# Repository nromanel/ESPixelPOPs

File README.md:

# ESPixel Pops

This is an attempted re-creation based on the original materials. It is not
the author's released board file.

A one-output Wi-Fi pixel controller for an ESP-01 module. The circuit is the
Ukewarrior ESPixel Pops rev D schematic of 19 July 2017. The board is 1.80 by
1.00 inch, so the 1.00 inch side slides into 1 inch schedule-40 PVC.

Every part on the board is through-hole. Open `ESPixelPOPs.kicad_pcb` in KiCad
8 and run Edit, Fill All Zones before ordering. GND is already traced on the
back; the zone is the pour.

- [ESPixel Pops project](https://zappedmyself.com/projects/espixelpops/) — [@packetbob](https://github.com/packetbob)
- [Original ESPixel](https://github.com/madsci1016/ESPixel) — [@madsci1016](https://github.com/madsci1016)

## How it matches the build guide

J1 is the 5-position 3.81 mm terminal, wire entries facing off the left edge.

| Pin | Silk | Connect |
|---|---|---|
| 1 | VCC | supply positive |
| 2 | GND | supply negative |
| 3 | GND | pixel ground |
| 4 | DATA | pixel data |
| 5 | VCC | pixel positive |

JP1 reads GND, CTS, VCC, RX, TX, DTR from left to right. For programming,
connect adapter ground to GND, adapter TXD to RX, and adapter RXD to TX. Leave
the other three pins open. VCC on this header is the pixel supply, not 3.3 V.
Power the board from J1. The adapter cannot run the ESP-01.

The ESP-01 plugs into U2 with the antenna hanging off the right edge. D1, the
1N4148, has its band toward the header. That diode is the serial level shifter,
so a 3.3 V or a 5 V adapter can program the module.

## 5 V pixels or 12 V pixels

U1 is an LD1117V33. Its metal tab is the 3.3 V output and faces the terminal.
Do not let the tab touch the terminal screws.

| Pixels | IC1 | Silk jumper |
|---|---|---|
| 5 V | leave it empty | solder a wire between pads 1 and 3 |
| 12 V | fit the 78L05, flat side toward R1 and R2 | no jumper |

Pad 1 is the square pad. On a 12 V build the 78L05 only feeds the pixel-data
pullup. The pixels themselves still get the full 12 V from J1 pin 5. A board
built one way does not drive the other kind of pixel.

Q1 is the 2N7000 data buffer. The flat faces the terminal. The top pad is the
source, the bottom pad is the drain, and the middle pin is the gate. GPIO2
drives the pixels. Hold S1 while powering the board to enter the serial bootloader.

## Firmware

ESPixelStick 3.2 is the last release that fits an ESP-01. Pixel output is
GPIO2. Later ESPixelStick releases need a module with 4 MB of flash.

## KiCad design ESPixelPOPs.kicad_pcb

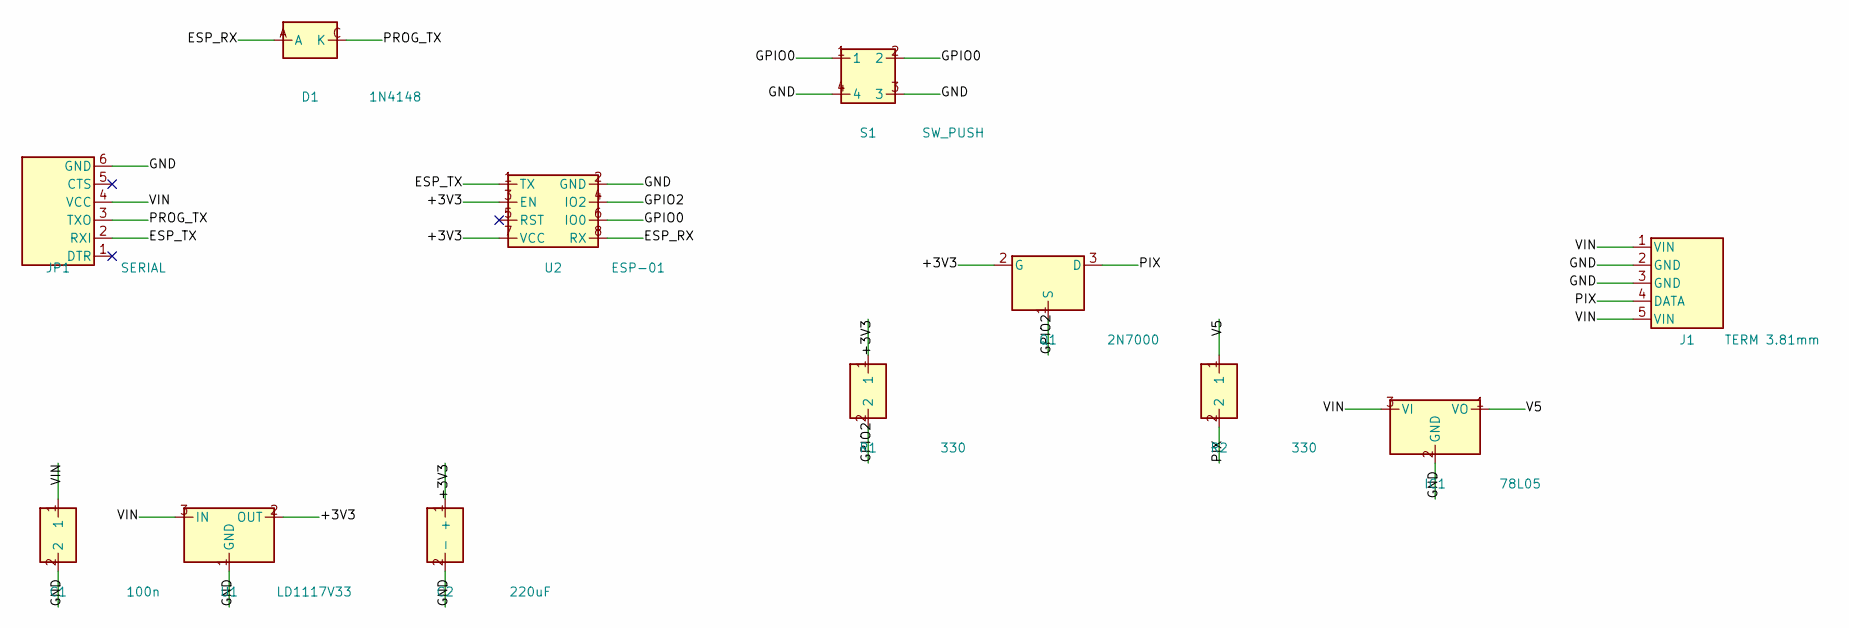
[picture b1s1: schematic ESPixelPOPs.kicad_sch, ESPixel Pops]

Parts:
C1: 100n; C_Disc_D5.0mm_W2.5mm_P2.54mm
C2: 220uF; CP_Radial_D5.0mm_P2.54mm
D1: 1N4148; D_DO-35_SOD27_P7.62mm_Vertical
IC1: 78L05; TO-92_Inline
J1: TERM 3.81mm; TerminalBlock_1x05_P3.81mm
JP1: SERIAL; PinHeader_1x06_P2.54mm_Vertical
Q1: 2N7000; TO-92_Inline
R1, R2: 330; R_Axial_DIN0207_L6.3mm_D2.5mm_P7.62mm
S1: SW_PUSH; SW_PUSH_6mm
U1: LD1117V33; TO-220-3_Vertical
U2: ESP-01; PinSocket_2x04_P2.54mm_Vertical

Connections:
+3V3: C2.1 (+), Q1.2 (G), R1.1, U1.2 (OUT), U2.3 (EN), U2.7 (VCC)
ESP_RX: D1.A, U2.8 (RX)
ESP_TX: JP1.2 (RXI), U2.1 (TX)
GND: C1.2, C2.2 (-), IC1.2 (GND), J1.2 (GND), J1.3 (GND), JP1.6 (GND), S1.3, S1.4, U1.1 (GND), U2.2 (GND)
GPIO0: S1.1, S1.2, U2.6 (IO0)
GPIO2: Q1.1 (S), R1.2, U2.4 (IO2)
PIX: J1.4 (DATA), Q1.3 (D), R2.2
PROG_TX: D1.C (K), JP1.3 (TXO)
V5: IC1.1 (VO), R2.1
VIN: C1.1, IC1.3 (VI), J1.1 (VIN), J1.5 (VIN), JP1.4 (VCC), U1.3 (IN)

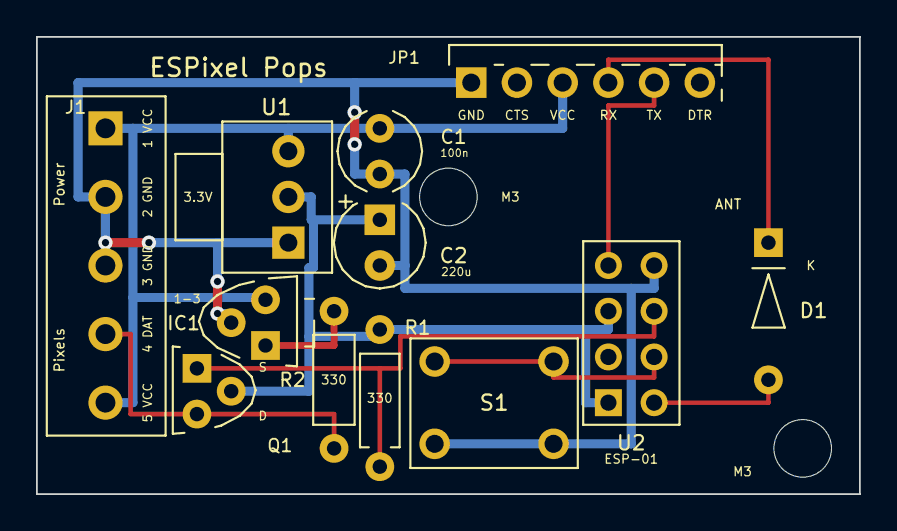
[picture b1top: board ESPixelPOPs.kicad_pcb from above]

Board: 2 copper layers, 45.7 x 25.4 mm, 12 parts (0 on the bottom side), 10 nets.

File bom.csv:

Qty,Ref,Value,Package,Notes
1,U1,LD1117V33,TO-220,"3.3 V regulator. Tab is VOUT and faces the terminal. Square pad is pin 1 GND."
1,IC1,LM78L05,TO-92,"12 V pixels only. Flat faces R1/R2. Omit for 5 V pixels and jumper pads 1 and 3."
1,Q1,2N7000,TO-92,"Flat faces the terminal. Top pad source, bottom pad drain, middle pad gate."
1,D1,1N4148,DO-35,"Band (cathode) toward the serial header."
2,"R1,R2",330 ohm 1/4W,axial 7.6 to 10 mm,"R2 is the left resistor."
1,C1,0.1 uF,ceramic 2.54 mm,50 V disc or MLCC
1,C2,220 uF 16 V,radial 5 mm,"Form leads to 2.54 mm. Square pad is positive."
1,S1,6 mm tact,6x6 mm through-hole,Fits only one way
1,JP1,1x6 male header,2.54 mm,"GND CTS VCC RX TX DTR left to right. Connect adapter GND, TXD to RX, RXD to TX."
1,U2,2x4 female socket,2.54 mm,"ESP-01. Antenna hangs off the right edge."
1,J1,5-pos screw terminal,3.81 mm,"Wire entries face off the left edge. 1 VCC, 2 GND, 3 GND, 4 DATA, 5 VCC."
1,,ESP-01,module,"1 MB flash is enough for ESPixelStick 3.2. Not supported by v4."
2,,M3 mounting hole,3.2 mm,25 mm apart, diagonally
